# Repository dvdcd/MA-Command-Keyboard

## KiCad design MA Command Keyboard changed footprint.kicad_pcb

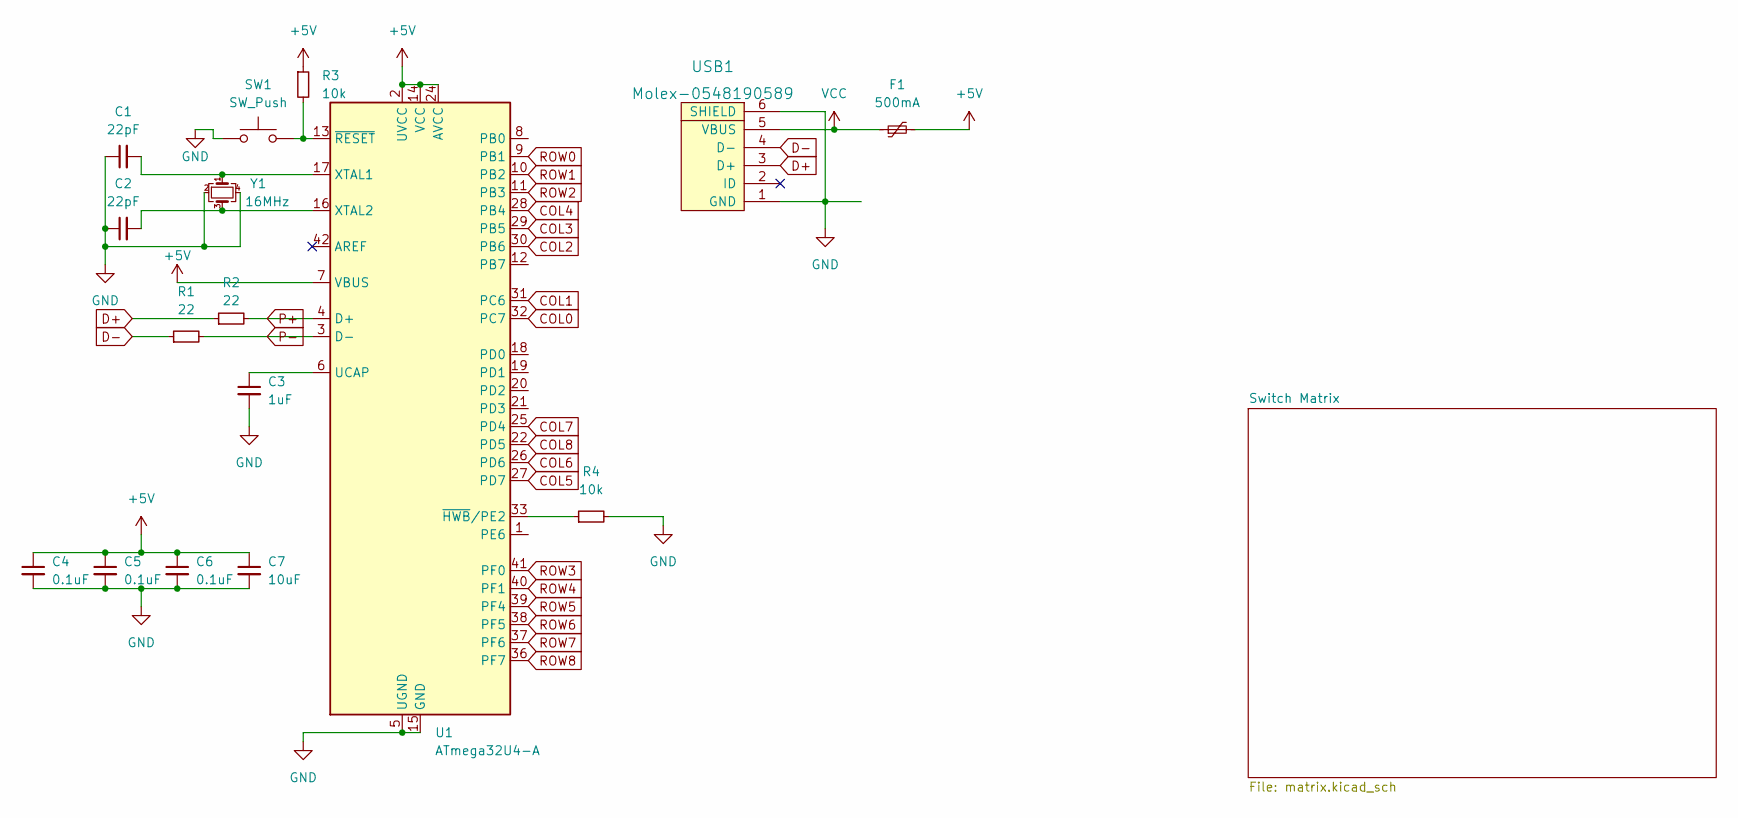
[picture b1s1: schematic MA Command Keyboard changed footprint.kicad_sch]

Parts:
C1, C2: 22pF; C_0805_2012Metric
C3: 1uF; C_0805_2012Metric
C4, C5, C6: 0.1uF; C_0805_2012Metric
C7: 10uF; C_0805_2012Metric
F1: 500mA; Fuse_1206_3216Metric
R1, R2: 22; R_0805_2012Metric
R3, R4: 10k; R_0805_2012Metric
SW1: SW_Push; SKQG-1155865
U1: ATmega32U4-A; TQFP-44_10x10mm_P0.8mm
USB1: Molex-0548190589
Y1: 16MHz; Crystal_SMD_3225-4Pin_3.2x2.5mm

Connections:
+5V: C4.1, C5.1, C6.1, C7.1, F1.2, R3.1, U1.2 (UVCC), U1.7 (VBUS), U1.14 (VCC), U1.24 (AVCC), U1.34 (VCC), U1.44 (AVCC)
COL0: U1.32 (PC7); also elsewhere on the board
COL1: U1.31 (PC6); also elsewhere on the board
COL2: U1.30 (PB6); also elsewhere on the board
COL3: U1.29 (PB5); also elsewhere on the board
COL4: U1.28 (PB4); also elsewhere on the board
COL5: U1.27 (PD7); also elsewhere on the board
COL6: U1.26 (PD6); also elsewhere on the board
COL7: U1.25 (PD4); also elsewhere on the board
COL8: U1.22 (PD5); also elsewhere on the board
D+: R2.1, USB1.3 (D+)
D-: R1.1, USB1.4 (D-)
GND: C1.1, C2.1, C3.2, C4.2, C5.2, C6.2, C7.2, R4.2, SW1.1, U1.5 (UGND), U1.15 (GND), U1.23 (GND), U1.35 (GND), U1.43 (GND), USB1.1 (GND), USB1.6 (SHIELD), Y1.2, Y1.4
unnamed: C1.2, U1.17 (XTAL1), Y1.1
unnamed: C2.2, U1.16 (XTAL2), Y1.3
unnamed: C3.1, U1.6 (UCAP)
unnamed: R3.2, SW1.2, U1.13 (~RESET)
unnamed: R4.1, U1.33 (~HWB/PE2)
P+: R2.2, U1.4 (D+)
P-: R1.2, U1.3 (D-)
ROW0: U1.9 (PB1); also elsewhere on the board
ROW1: U1.10 (PB2); also elsewhere on the board
ROW2: U1.11 (PB3); also elsewhere on the board
ROW3: U1.41 (PF0); also elsewhere on the board
ROW4: U1.40 (PF1); also elsewhere on the board
ROW5: U1.39 (PF4); also elsewhere on the board
ROW6: U1.38 (PF5); also elsewhere on the board
ROW7: U1.37 (PF6); also elsewhere on the board
ROW8: U1.36 (PF7); also elsewhere on the board
VCC: F1.1, USB1.5 (VBUS)

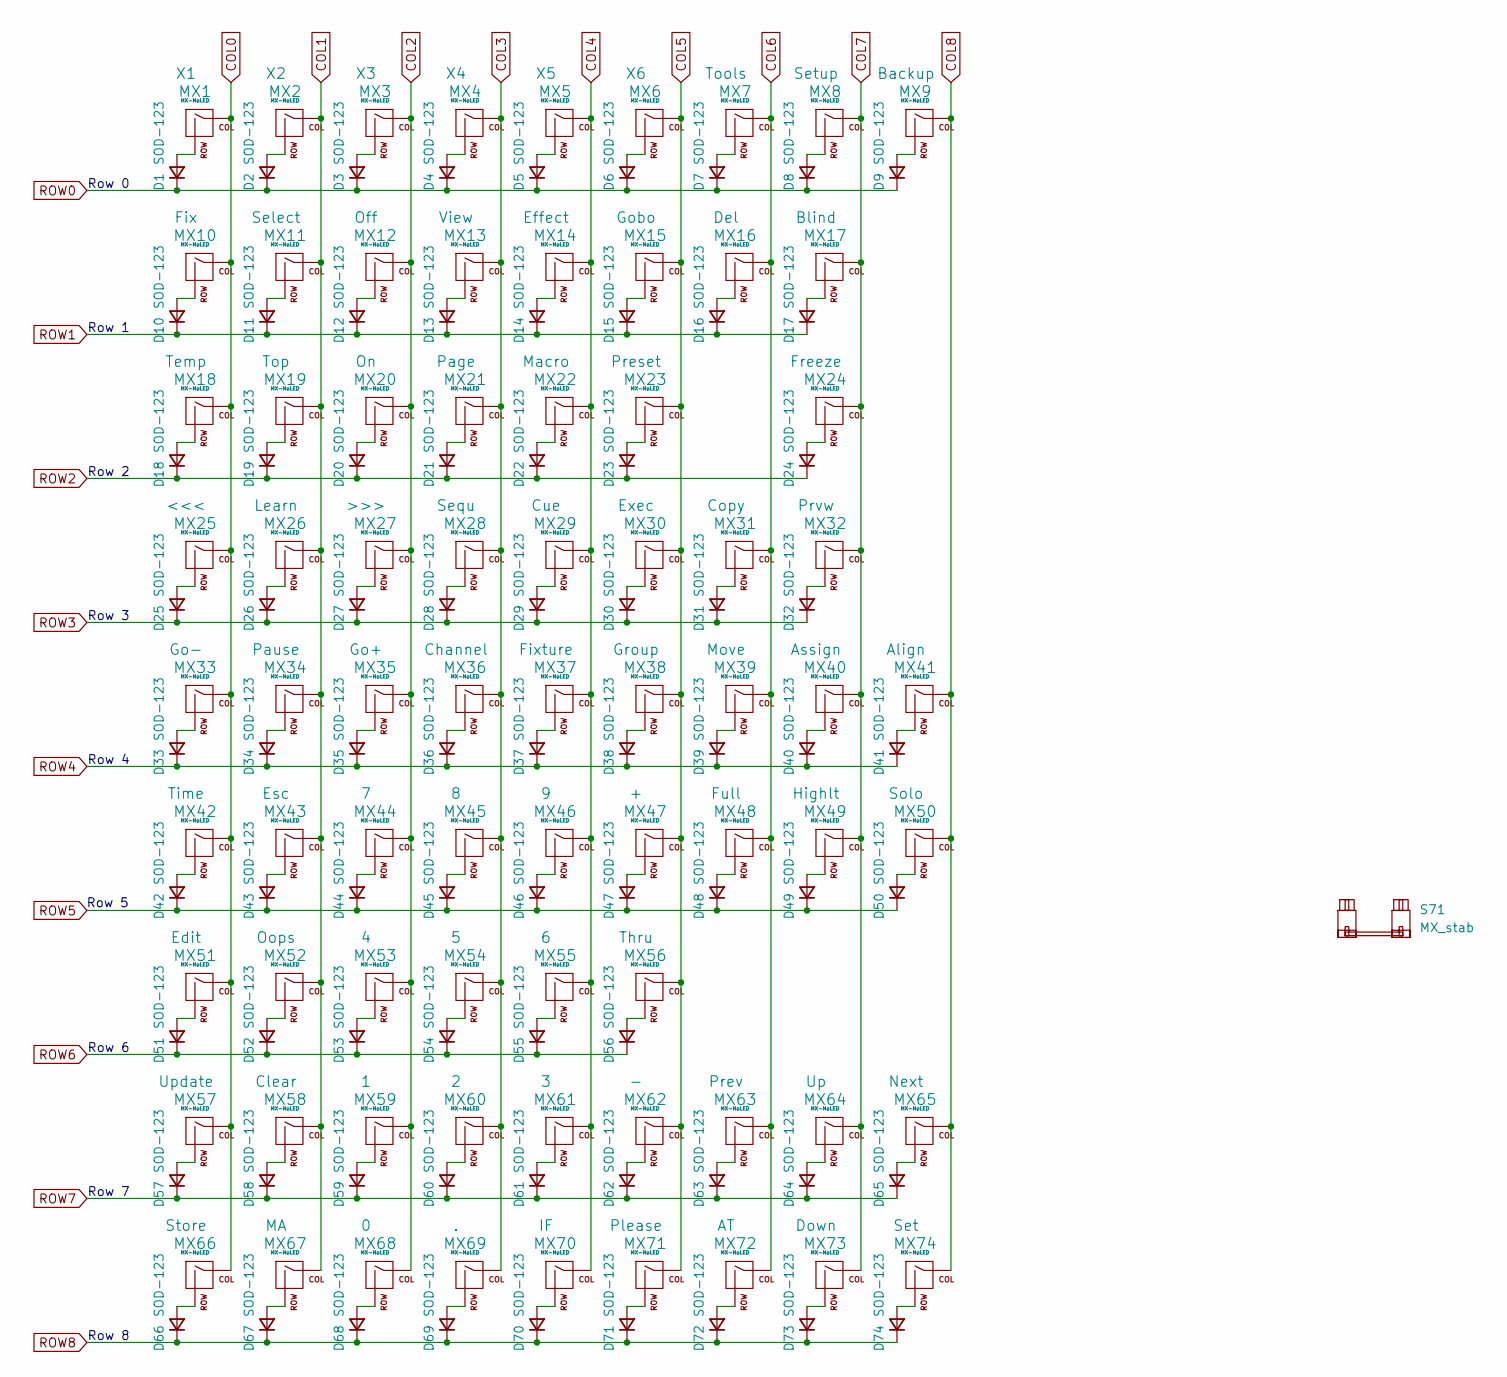
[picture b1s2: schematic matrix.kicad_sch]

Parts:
D1, D2, D3, D4, D5, D6, D7, D8, D9, D10, D11, D12, D13, D14, D15, D16, D17, D18, D19, D20, D21, D22, D23, D24, D25, D26, D27, D28, D29, D30, D31, D32, D33, D34, D35, D36, D37, D38, D39, D40, D41, D42, D43, D44, D45, D46, D47, D48, D49, D50, D51, D52, D53, D54, D55, D56, D57, D58, D59, D60, D61, D62, D63, D64, D65, D66, D67, D68, D69, D70, D71, D72, D73, D74: SOD-123; D_SOD-123
MX1, MX2, MX3, MX4, MX5, MX6, MX7, MX8, MX9, MX10, MX11, MX12, MX13, MX14, MX15, MX16, MX17, MX18, MX19, MX20, MX21, MX22, MX23, MX24, MX25, MX26, MX27, MX28, MX29, MX30, MX31, MX32, MX33, MX34, MX35, MX36, MX37, MX38, MX39, MX40, MX41, MX42, MX43, MX44, MX45, MX46, MX47, MX48, MX49, MX50, MX51, MX52, MX53, MX54, MX55, MX56, MX57, MX58, MX59, MX60, MX61, MX62, MX63, MX64, MX65, MX66, MX67, MX68, MX69, MX70, MX71, MX72, MX73, MX74: MX-NoLED; MXOnly-1U-Hotswap-Antishear-Dvdcd-Mod
S71: MX_stab; STAB_MX_2u

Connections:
COL0: MX1.1 (COL), MX10.1 (COL), MX18.1 (COL), MX25.1 (COL), MX33.1 (COL), MX42.1 (COL), MX51.1 (COL), MX57.1 (COL), MX66.1 (COL); also elsewhere on the board
COL1: MX2.1 (COL), MX11.1 (COL), MX19.1 (COL), MX26.1 (COL), MX34.1 (COL), MX43.1 (COL), MX52.1 (COL), MX58.1 (COL), MX67.1 (COL); also elsewhere on the board
COL2: MX3.1 (COL), MX12.1 (COL), MX20.1 (COL), MX27.1 (COL), MX35.1 (COL), MX44.1 (COL), MX53.1 (COL), MX59.1 (COL), MX68.1 (COL); also elsewhere on the board
COL3: MX4.1 (COL), MX13.1 (COL), MX21.1 (COL), MX28.1 (COL), MX36.1 (COL), MX45.1 (COL), MX54.1 (COL), MX60.1 (COL), MX69.1 (COL); also elsewhere on the board
COL4: MX5.1 (COL), MX14.1 (COL), MX22.1 (COL), MX29.1 (COL), MX37.1 (COL), MX46.1 (COL), MX55.1 (COL), MX61.1 (COL), MX70.1 (COL); also elsewhere on the board
COL5: MX6.1 (COL), MX15.1 (COL), MX23.1 (COL), MX30.1 (COL), MX38.1 (COL), MX47.1 (COL), MX56.1 (COL), MX62.1 (COL), MX71.1 (COL); also elsewhere on the board
COL6: MX7.1 (COL), MX16.1 (COL), MX31.1 (COL), MX39.1 (COL), MX48.1 (COL), MX63.1 (COL), MX72.1 (COL); also elsewhere on the board
COL7: MX8.1 (COL), MX17.1 (COL), MX24.1 (COL), MX32.1 (COL), MX40.1 (COL), MX49.1 (COL), MX64.1 (COL), MX73.1 (COL); also elsewhere on the board
COL8: MX9.1 (COL), MX41.1 (COL), MX50.1 (COL), MX65.1 (COL), MX74.1 (COL); also elsewhere on the board
unnamed: D1.2 (A), MX1.2 (ROW)
unnamed: D2.2 (A), MX2.2 (ROW)
unnamed: D3.2 (A), MX3.2 (ROW)
unnamed: D4.2 (A), MX4.2 (ROW)
unnamed: D5.2 (A), MX5.2 (ROW)
unnamed: D6.2 (A), MX6.2 (ROW)
unnamed: D7.2 (A), MX7.2 (ROW)
unnamed: D8.2 (A), MX8.2 (ROW)
unnamed: D9.2 (A), MX9.2 (ROW)
unnamed: D10.2 (A), MX10.2 (ROW)
unnamed: D11.2 (A), MX11.2 (ROW)
unnamed: D12.2 (A), MX12.2 (ROW)
unnamed: D13.2 (A), MX13.2 (ROW)
unnamed: D14.2 (A), MX14.2 (ROW)
unnamed: D15.2 (A), MX15.2 (ROW)
unnamed: D16.2 (A), MX16.2 (ROW)
unnamed: D17.2 (A), MX17.2 (ROW)
unnamed: D18.2 (A), MX18.2 (ROW)
unnamed: D19.2 (A), MX19.2 (ROW)
unnamed: D20.2 (A), MX20.2 (ROW)
unnamed: D21.2 (A), MX21.2 (ROW)
unnamed: D22.2 (A), MX22.2 (ROW)
unnamed: D23.2 (A), MX23.2 (ROW)
unnamed: D24.2 (A), MX24.2 (ROW)
unnamed: D25.2 (A), MX25.2 (ROW)
unnamed: D26.2 (A), MX26.2 (ROW)
unnamed: D27.2 (A), MX27.2 (ROW)
unnamed: D28.2 (A), MX28.2 (ROW)
unnamed: D29.2 (A), MX29.2 (ROW)
unnamed: D30.2 (A), MX30.2 (ROW)
unnamed: D31.2 (A), MX31.2 (ROW)
unnamed: D32.2 (A), MX32.2 (ROW)
unnamed: D33.2 (A), MX33.2 (ROW)
unnamed: D34.2 (A), MX34.2 (ROW)
unnamed: D35.2 (A), MX35.2 (ROW)
unnamed: D36.2 (A), MX36.2 (ROW)
unnamed: D37.2 (A), MX37.2 (ROW)
unnamed: D38.2 (A), MX38.2 (ROW)
unnamed: D39.2 (A), MX39.2 (ROW)
unnamed: D40.2 (A), MX40.2 (ROW)
unnamed: D41.2 (A), MX41.2 (ROW)
unnamed: D42.2 (A), MX42.2 (ROW)
unnamed: D43.2 (A), MX43.2 (ROW)
unnamed: D44.2 (A), MX44.2 (ROW)
unnamed: D45.2 (A), MX45.2 (ROW)
unnamed: D46.2 (A), MX46.2 (ROW)
unnamed: D47.2 (A), MX47.2 (ROW)
unnamed: D48.2 (A), MX48.2 (ROW)
unnamed: D49.2 (A), MX49.2 (ROW)
unnamed: D50.2 (A), MX50.2 (ROW)
unnamed: D51.2 (A), MX51.2 (ROW)
unnamed: D52.2 (A), MX52.2 (ROW)
unnamed: D53.2 (A), MX53.2 (ROW)
unnamed: D54.2 (A), MX54.2 (ROW)
unnamed: D55.2 (A), MX55.2 (ROW)
unnamed: D56.2 (A), MX56.2 (ROW)
unnamed: D57.2 (A), MX57.2 (ROW)
unnamed: D58.2 (A), MX58.2 (ROW)
unnamed: D59.2 (A), MX59.2 (ROW)
unnamed: D60.2 (A), MX60.2 (ROW)
unnamed: D61.2 (A), MX61.2 (ROW)
unnamed: D62.2 (A), MX62.2 (ROW)
unnamed: D63.2 (A), MX63.2 (ROW)
unnamed: D64.2 (A), MX64.2 (ROW)
unnamed: D65.2 (A), MX65.2 (ROW)
unnamed: D66.2 (A), MX66.2 (ROW)
unnamed: D67.2 (A), MX67.2 (ROW)
unnamed: D68.2 (A), MX68.2 (ROW)
unnamed: D69.2 (A), MX69.2 (ROW)
unnamed: D70.2 (A), MX70.2 (ROW)
unnamed: D71.2 (A), MX71.2 (ROW)
unnamed: D72.2 (A), MX72.2 (ROW)
unnamed: D73.2 (A), MX73.2 (ROW)
unnamed: D74.2 (A), MX74.2 (ROW)
ROW0: D1.1 (K), D2.1 (K), D3.1 (K), D4.1 (K), D5.1 (K), D6.1 (K), D7.1 (K), D8.1 (K), D9.1 (K); also elsewhere on the board
ROW1: D10.1 (K), D11.1 (K), D12.1 (K), D13.1 (K), D14.1 (K), D15.1 (K), D16.1 (K), D17.1 (K); also elsewhere on the board
ROW2: D18.1 (K), D19.1 (K), D20.1 (K), D21.1 (K), D22.1 (K), D23.1 (K), D24.1 (K); also elsewhere on the board
ROW3: D25.1 (K), D26.1 (K), D27.1 (K), D28.1 (K), D29.1 (K), D30.1 (K), D31.1 (K), D32.1 (K); also elsewhere on the board
ROW4: D33.1 (K), D34.1 (K), D35.1 (K), D36.1 (K), D37.1 (K), D38.1 (K), D39.1 (K), D40.1 (K), D41.1 (K); also elsewhere on the board
ROW5: D42.1 (K), D43.1 (K), D44.1 (K), D45.1 (K), D46.1 (K), D47.1 (K), D48.1 (K), D49.1 (K), D50.1 (K); also elsewhere on the board
ROW6: D51.1 (K), D52.1 (K), D53.1 (K), D54.1 (K), D55.1 (K), D56.1 (K); also elsewhere on the board
ROW7: D57.1 (K), D58.1 (K), D59.1 (K), D60.1 (K), D61.1 (K), D62.1 (K), D63.1 (K), D64.1 (K), D65.1 (K); also elsewhere on the board
ROW8: D66.1 (K), D67.1 (K), D68.1 (K), D69.1 (K), D70.1 (K), D71.1 (K), D72.1 (K), D73.1 (K), D74.1 (K); also elsewhere on the board

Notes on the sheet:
Row 8
Row 3
Row 4
Row 7
Row 5
Row 6
Row 1
Row 2
Row 0

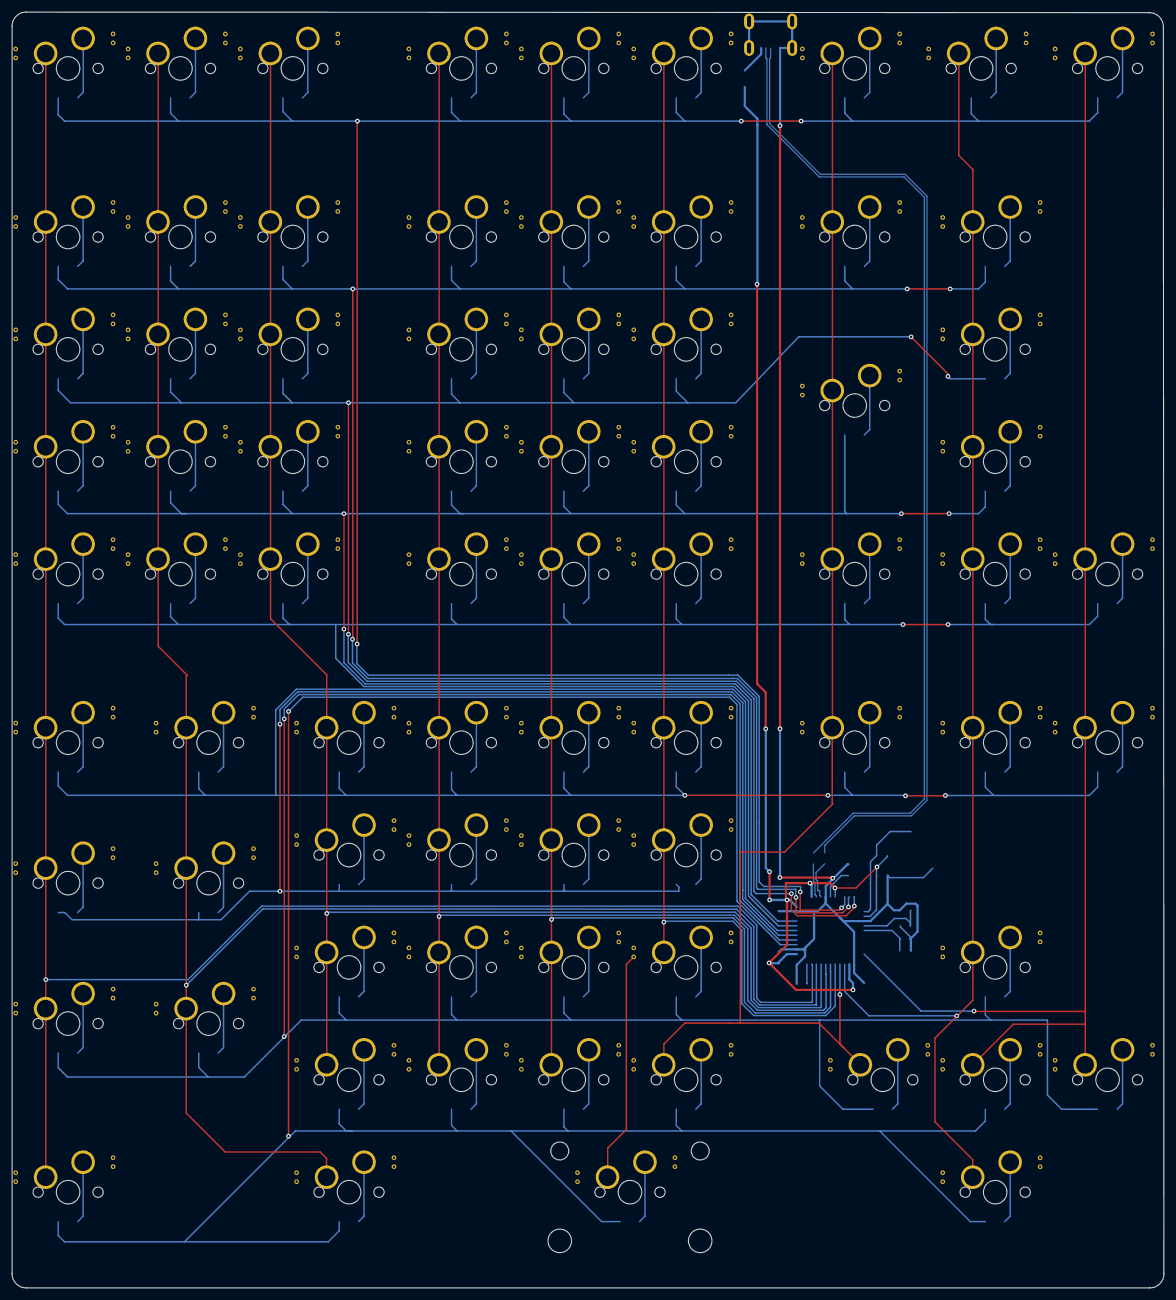
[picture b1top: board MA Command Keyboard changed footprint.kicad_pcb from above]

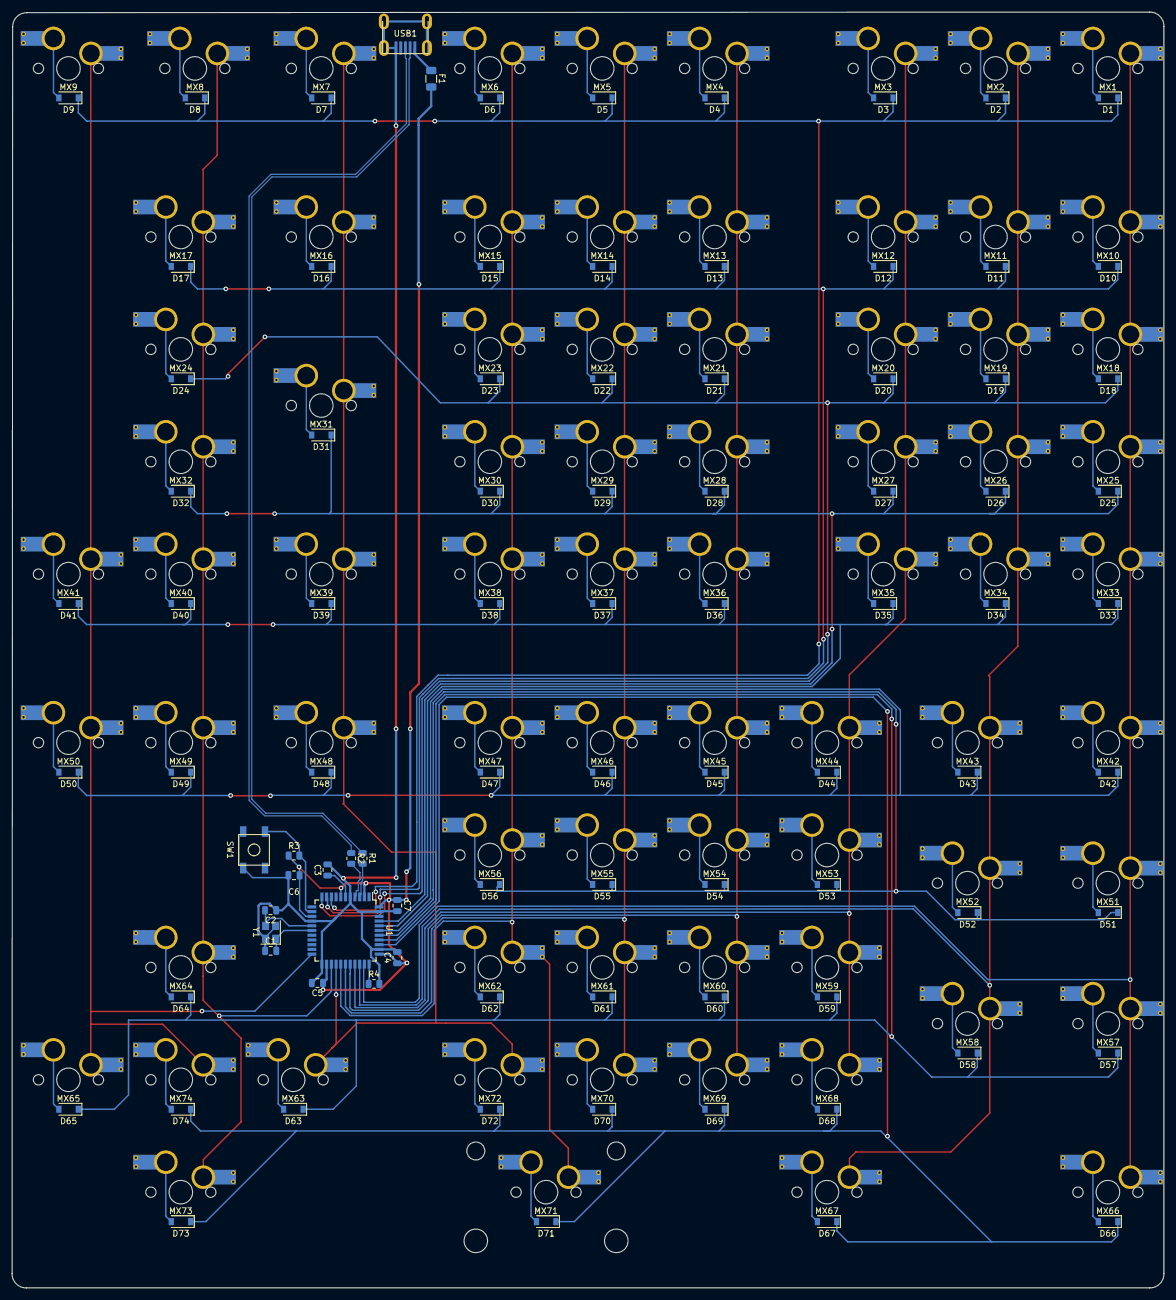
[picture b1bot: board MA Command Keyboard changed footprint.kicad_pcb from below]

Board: 2 copper layers, 195.3 x 216.3 mm, 165 parts (90 on the bottom side), 104 nets.

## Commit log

2023-02-04 Add Submodules and init kicad
2023-02-04 Adding Libs into KiCad
2023-02-04 Everything but switch matrix
2023-02-04 Add ai03's symbols
2023-02-04 Placing Finished
2023-02-04 Update Layout and Ref
2023-02-04 Updated Placement
2023-02-04 Matrix Traces in
2023-02-05 Traces First Draft
